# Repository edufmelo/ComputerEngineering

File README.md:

Academic projects and exercises developed during the Computer Engineering course.
(If there is any File/Folder that is not opening, it already has a specific repository on my GitHub.)
Last User - Eduardo Melo
Correct User - edufmelo

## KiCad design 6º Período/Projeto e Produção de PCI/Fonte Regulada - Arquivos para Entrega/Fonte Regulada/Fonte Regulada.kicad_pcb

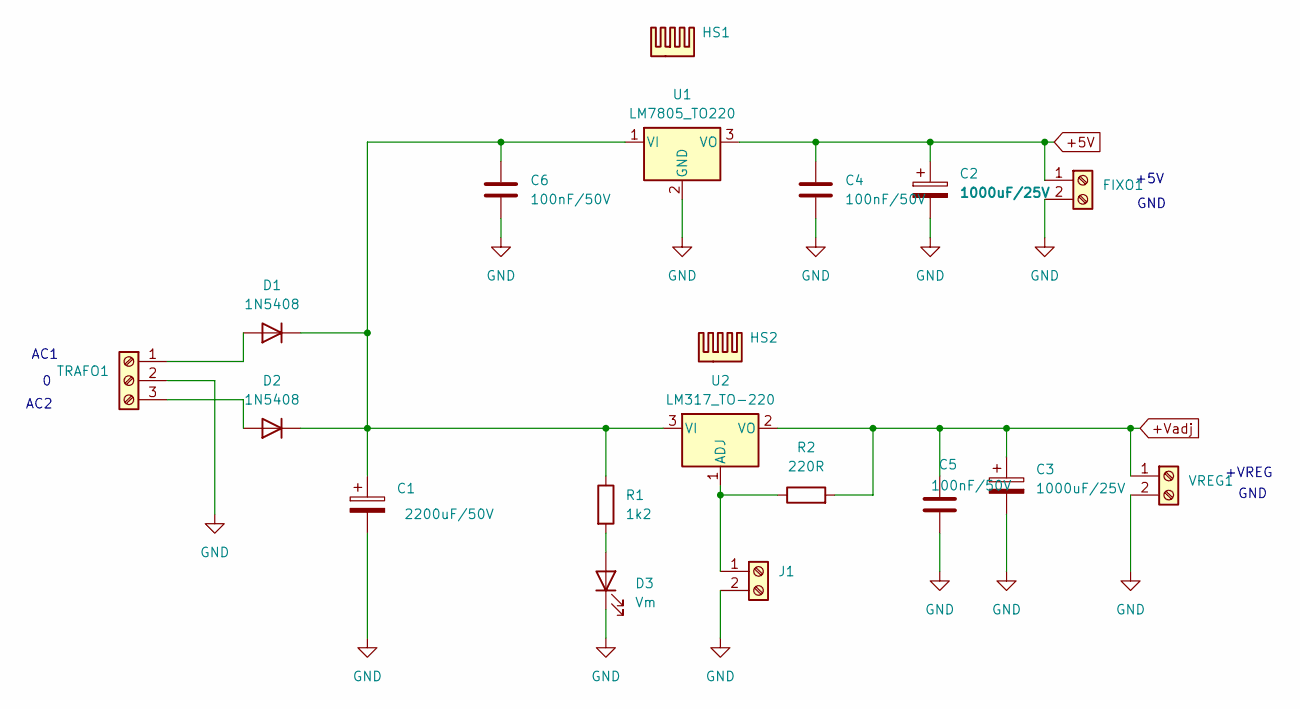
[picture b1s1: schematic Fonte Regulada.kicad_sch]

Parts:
C1: 2200uF/50V; CP_Radial_D17.0mm_P7.50mm
C2, C3: 1000uF/25V; CP_Radial_D10.0mm_P5.00mm
C4, C5, C6: 100nF/50V; C_Disc_D5.1mm_W3.2mm_P5.00mm
D1, D2: 1N5408; D_DO-201AD_P15.24mm_Horizontal
D3: Vm; LED_D5.0mm
FIXO1: TerminalBlock_Phoenix_MKDS-1,5-2-5.08_1x02_P5.08mm_Horizont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
HS1, HS2: Heatsink; Heatsink_35x26mm_1xFixation3mm_Fischer-SK486-35
J1: Screw_Terminal_01x02; TerminalBlock_Phoenix_MKDS-1,5-2-5.08_1x02_P5.08mm_Horizont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
R1: 1k2; R_Axial_DIN0207_L6.3mm_D2.5mm_P10.16mm_Horizontal
R2: 220R; R_Axial_DIN0207_L6.3mm_D2.5mm_P10.16mm_Horizontal
TRAFO1: TerminalBlock_Phoenix_MKDS-1,5-3-5.08_1x03_P5.08mm_Horizont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
U1: LM7805_TO220; TO-220-3_Horizontal_TabDown
U2: LM317_TO-220; TO-220-3_Horizontal_TabDown
VREG1: TerminalBlock_Phoenix_MKDS-1,5-2-5.08_1x02_P5.08mm_Horizont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

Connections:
+5V: C2.1, C4.1, FIXO1.1, U1.3 (VO)
+Vadj: C3.1, C5.1, R2.2, U2.2 (VO), VREG1.1
GND: C1.2, C2.2, C3.2, C4.2, C5.2, C6.2, D3.1 (K), FIXO1.2, J1.2, TRAFO1.2, U1.2 (GND), VREG1.2
unnamed: D1.2 (A), TRAFO1.1
unnamed: C1.1, C6.1, D1.1 (K), D2.1 (K), R1.1, U1.1 (VI), U2.3 (VI)
unnamed: D2.2 (A), TRAFO1.3
unnamed: D3.2 (A), R1.2
unnamed: J1.1, R2.1, U2.1 (ADJ)

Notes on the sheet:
+VREG
AC1
GND
+5V
AC2
GND

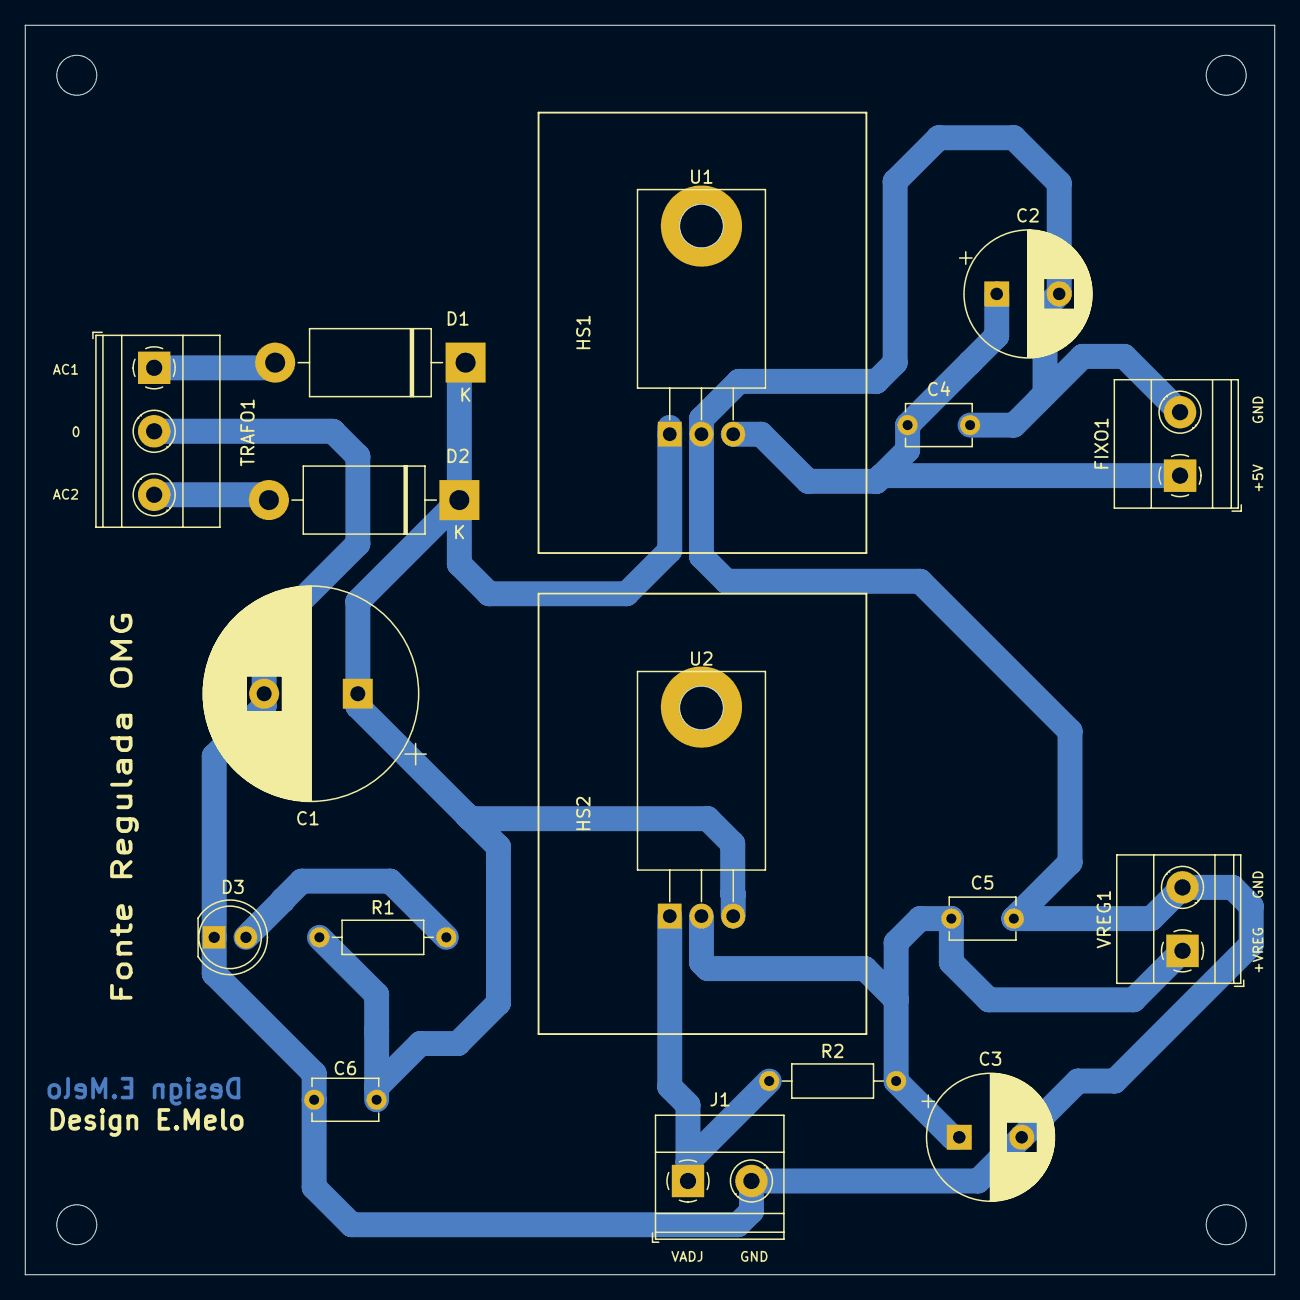
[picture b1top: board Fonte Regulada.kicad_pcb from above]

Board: 2 copper layers, 100.0 x 100.0 mm, 19 parts (0 on the bottom side), 8 nets.

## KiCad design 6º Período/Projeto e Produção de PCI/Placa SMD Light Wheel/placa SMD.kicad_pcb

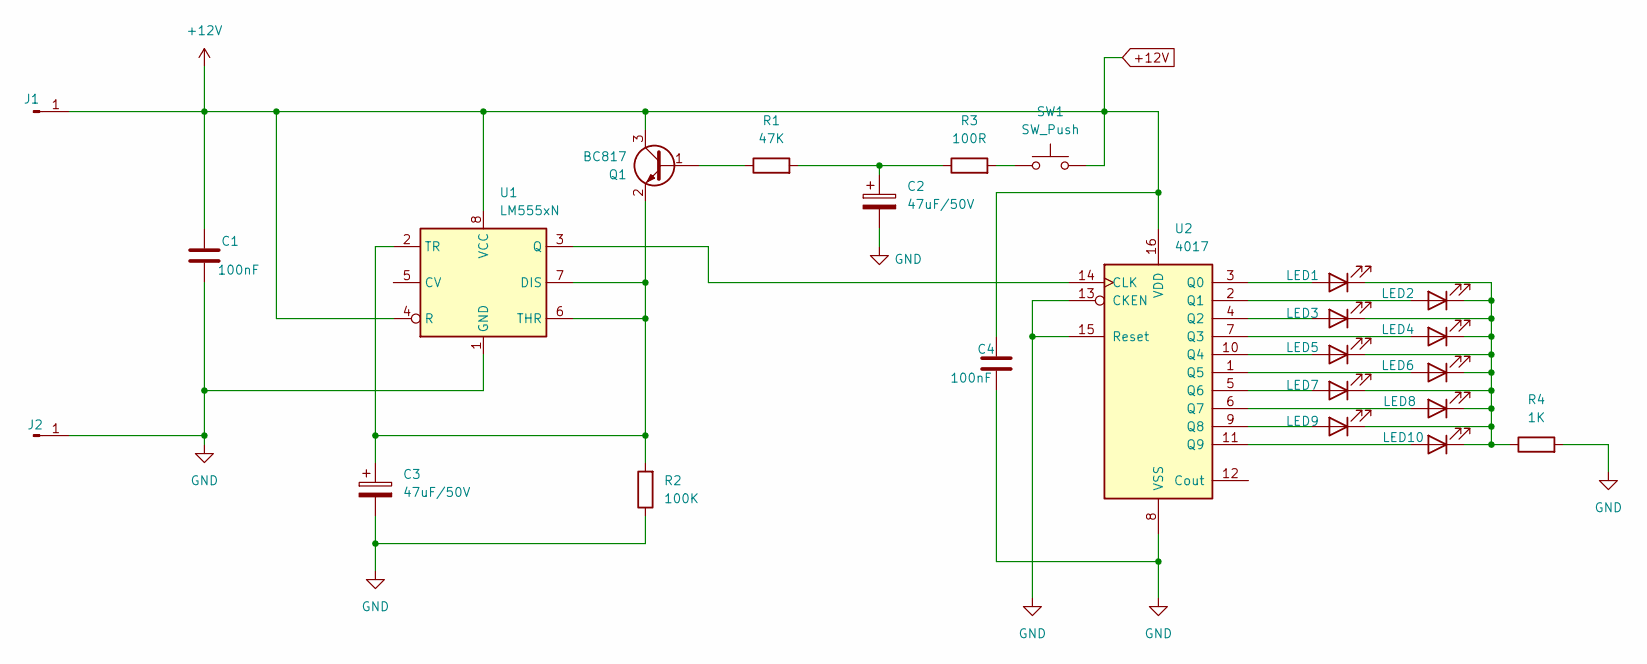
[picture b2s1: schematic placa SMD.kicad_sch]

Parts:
C1, C4: 100nF; C_0805_2012Metric
C2, C3: 47uF/50V; CP_Elec_5x5.9
D1: LED1; LED_0805_2012Metric
D2: LED2; LED_0805_2012Metric
D3: LED3; LED_0805_2012Metric
D4: LED4; LED_0805_2012Metric
D5: LED5; LED_0805_2012Metric
D6: LED6; LED_0805_2012Metric
D7: LED7; LED_0805_2012Metric
D8: LED8; LED_0805_2012Metric
D9: LED9; LED_0805_2012Metric
D10: LED10; LED_0805_2012Metric
J1, J2: Conn_01x01_Pin; PinHeader_1x01_P2.54mm_Vertical
Q1: BC817; SOT-23
R1: 47K; R_0805_2012Metric
R2: 100K; R_0805_2012Metric
R3: 100R; R_0805_2012Metric
R4: 1K; R_0805_2012Metric
SW1: SW_Push; SW_SPST_FSMSM
U1: LM555xN; SOIC-8-1EP_3.9x4.9mm_P1.27mm_EP2.29x3mm
U2: 4017; SOP-16_4.4x10.4mm_P1.27mm

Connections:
+12V: C1.1, C4.1, J1.1, Q1.3 (C), SW1.2, U1.4 (R), U1.8 (VCC), U2.16 (VDD); also elsewhere on the board
GND: C1.2, C2.2, C3.2, C4.2, J2.1, R2.1, R4.2, U1.1 (GND), U2.8 (VSS), U2.13 (CKEN), U2.15 (Reset); also elsewhere on the board
unnamed: C2.1, R1.2, R3.1
unnamed: D1.2 (A), U2.3 (Q0)
unnamed: D1.1 (K), D2.1 (K), D3.1 (K), D4.1 (K), D5.1 (K), D6.1 (K), D7.1 (K), D8.1 (K), D9.1 (K), D10.1 (K), R4.1
unnamed: D2.2 (A), U2.2 (Q1)
unnamed: D3.2 (A), U2.4 (Q2)
unnamed: D4.2 (A), U2.7 (Q3)
unnamed: D5.2 (A), U2.10 (Q4)
unnamed: D6.2 (A), U2.1 (Q5)
unnamed: D7.2 (A), U2.5 (Q6)
unnamed: D8.2 (A), U2.6 (Q7)
unnamed: D9.2 (A), U2.9 (Q8)
unnamed: D10.2 (A), U2.11 (Q9)
unnamed: Q1.1 (B), R1.1
unnamed: C3.1, Q1.2 (E), R2.2, U1.2 (TR), U1.6 (THR), U1.7 (DIS)
unnamed: R3.2, SW1.1
unnamed: U1.3 (Q), U2.14 (CLK)

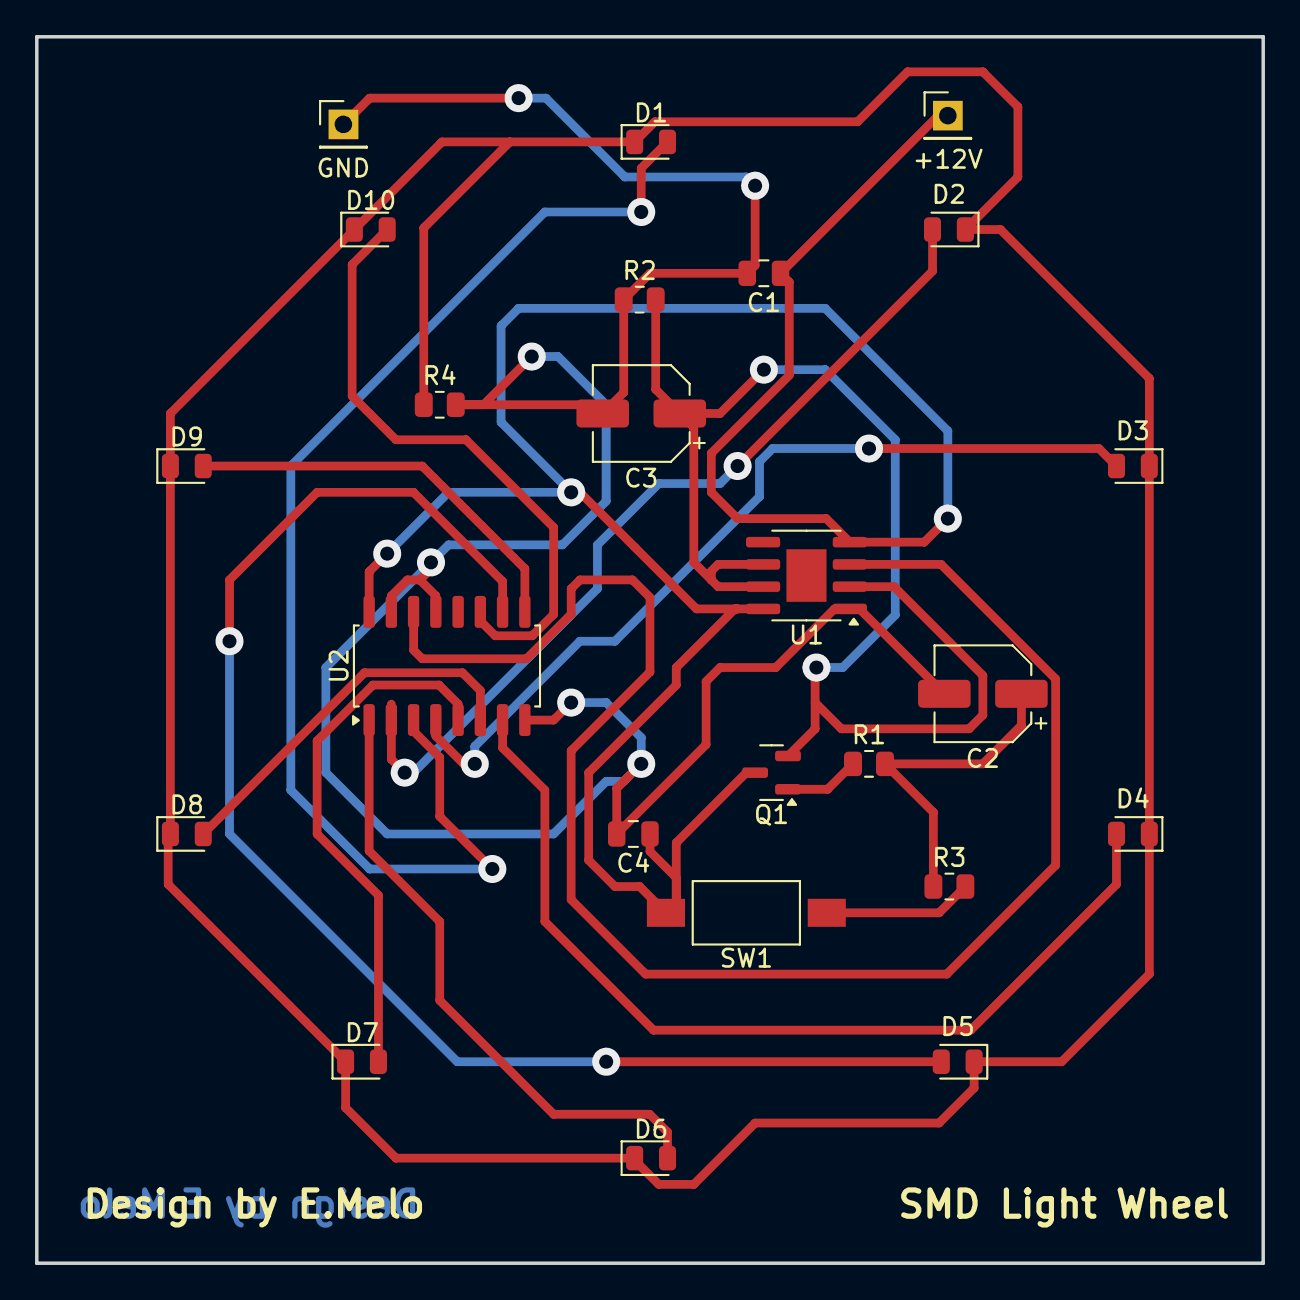
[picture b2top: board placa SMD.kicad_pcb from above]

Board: 2 copper layers, 70.0 x 70.0 mm, 24 parts (0 on the bottom side), 18 nets.

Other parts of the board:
+12V: Conn_01x01_Pin; PinHeader_1x01_P2.54mm_Vertical
GND: Conn_01x01_Pin; PinHeader_1x01_P2.54mm_Vertical

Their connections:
+12V: +12V.1; also elsewhere on the board
GND: GND.1; also elsewhere on the board

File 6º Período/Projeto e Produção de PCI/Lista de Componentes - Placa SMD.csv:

"Reference","Value","Datasheet","Footprint","Qty","DNP"
"C1,C4","100nF","~","Capacitor_SMD:C_0805_2012Metric","2",""
"C2,C3","47uF/50V","~","Capacitor_SMD:CP_Elec_5x5.9","2",""
"D1","LED1","~","LED_SMD:LED_0805_2012Metric","1",""
"D2","LED2","~","LED_SMD:LED_0805_2012Metric","1",""
"D3","LED3","~","LED_SMD:LED_0805_2012Metric","1",""
"D4","LED4","~","LED_SMD:LED_0805_2012Metric","1",""
"D5","LED5","~","LED_SMD:LED_0805_2012Metric","1",""
"D6","LED6","~","LED_SMD:LED_0805_2012Metric","1",""
"D7","LED7","~","LED_SMD:LED_0805_2012Metric","1",""
"D8","LED8","~","LED_SMD:LED_0805_2012Metric","1",""
"D9","LED9","~","LED_SMD:LED_0805_2012Metric","1",""
"D10","LED10","~","LED_SMD:LED_0805_2012Metric","1",""
"J1,J2","Conn_01x01_Pin","~","-- valores mistos --","2",""
"Q1","BC817","https://www.onsemi.com/pub/Collateral/BC818-D.pdf","Package_TO_SOT_SMD:SOT-23","1",""
"R1","47K","~","Resistor_SMD:R_0805_2012Metric","1",""
"R2","100K","~","Resistor_SMD:R_0805_2012Metric","1",""
"R3","100R","~","Resistor_SMD:R_0805_2012Metric","1",""
"R4","1K","~","Resistor_SMD:R_0805_2012Metric","1",""
"SW1","SW_Push","~","Button_Switch_SMD:SW_SPST_FSMSM","1",""
"U1","LM555xN","http://www.ti.com/lit/ds/symlink/lm555.pdf","Package_SO:SOIC-8_3.9x4.9mm_P1.27mm","1",""
"U2","4017","http://www.intersil.com/content/dam/Intersil/documents/cd40/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","Package_SO:SOP-16_4.4x10.4mm_P1.27mm","1",""

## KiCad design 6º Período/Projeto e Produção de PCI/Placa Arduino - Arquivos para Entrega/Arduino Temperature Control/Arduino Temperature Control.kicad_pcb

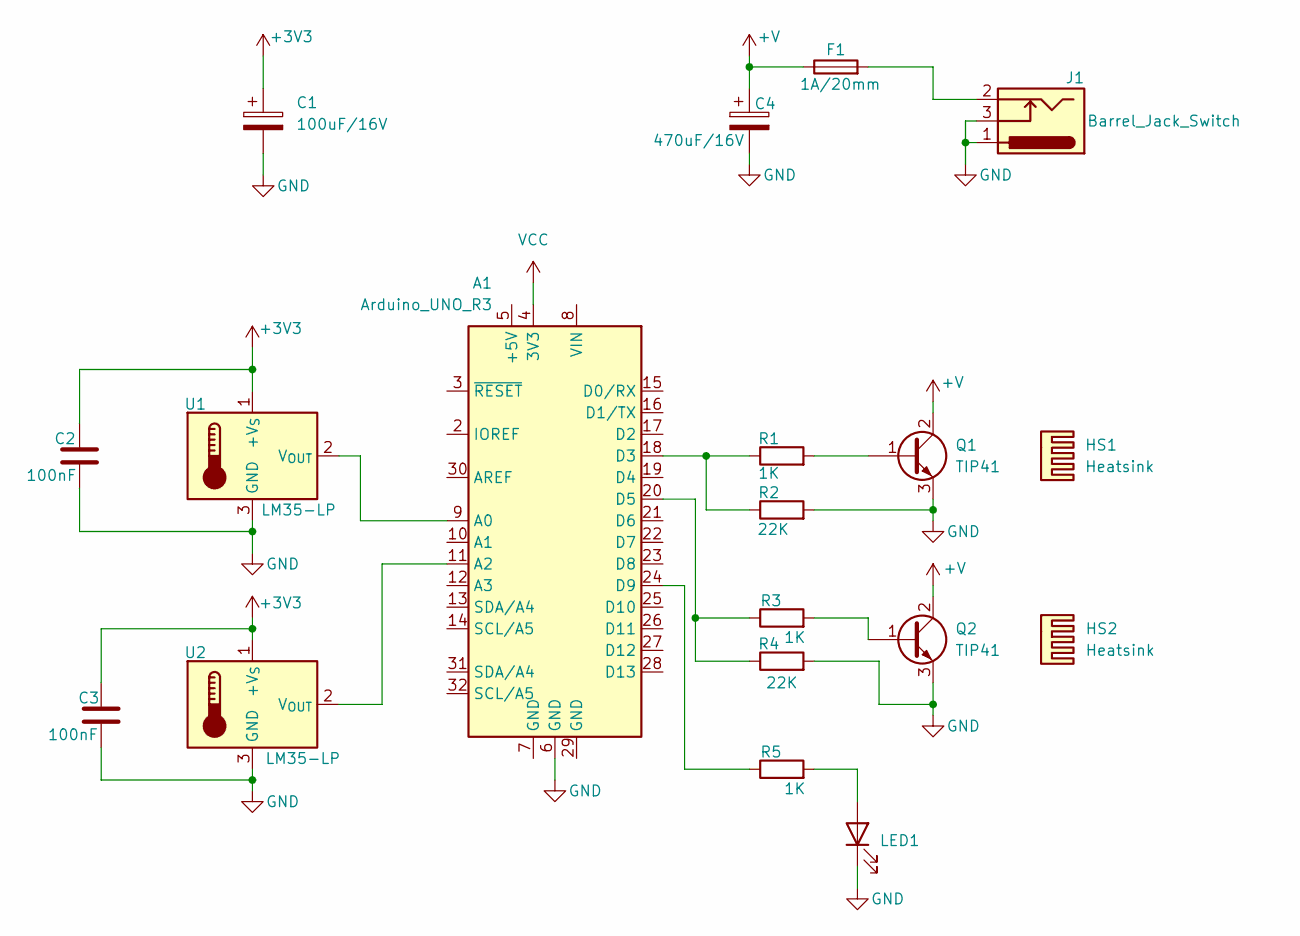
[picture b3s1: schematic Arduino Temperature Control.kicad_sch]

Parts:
A1: Arduino_UNO_R3
C1: 100uF/16V; CP_Radial_D10.0mm_P5.00mm
C2, C3: 100nF; C_Disc_D5.1mm_W3.2mm_P5.00mm
C4: 470uF/16V; CP_Radial_D10.0mm_P5.00mm
D1: LED1; LED_D5.0mm
F1: 1A/20mm; Fuseholder_Clip-5x20mm_Keystone_3517_Inline_P23.11x6.76mm_D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
HS1, HS2: Heatsink; Heatsink_Stonecold_HS-S02_13.21x9.53mm
J1: Barrel_Jack_Switch; BarrelJack_Horizontal
Q1, Q2: TIP41; TO-220-3_Vertical
R1, R3, R5: 1K; R_Axial_DIN0207_L6.3mm_D2.5mm_P10.16mm_Horizontal
R2, R4: 22K; R_Axial_DIN0207_L6.3mm_D2.5mm_P10.16mm_Horizontal
U1, U2: LM35-LP; TO-92_Inline

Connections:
+3V3: C1.1, C2.1, C3.1, U1.1 (+V_{S}), U2.1 (+V_{S})
+V: C4.1, F1.1, Q1.2 (C), Q2.2 (C)
GND: A1.6 (GND), C1.2, C2.2, C3.2, C4.2, D1.1 (K), J1.1, J1.3, Q1.3 (E), Q2.3 (E), R2.2, R4.2, U1.3 (GND), U2.3 (GND)
unnamed: A1.9 (A0), U1.2 (V_{OUT})
unnamed: A1.11 (A2), U2.2 (V_{OUT})
unnamed: A1.18 (D3), R1.1, R2.1
unnamed: A1.20 (D5), R3.1, R4.1
unnamed: A1.24 (D9), R5.1
unnamed: D1.2 (A), R5.2
unnamed: F1.2, J1.2
unnamed: Q1.1 (B), R1.2
unnamed: Q2.1 (B), R3.2
VCC: A1.4 (3V3)

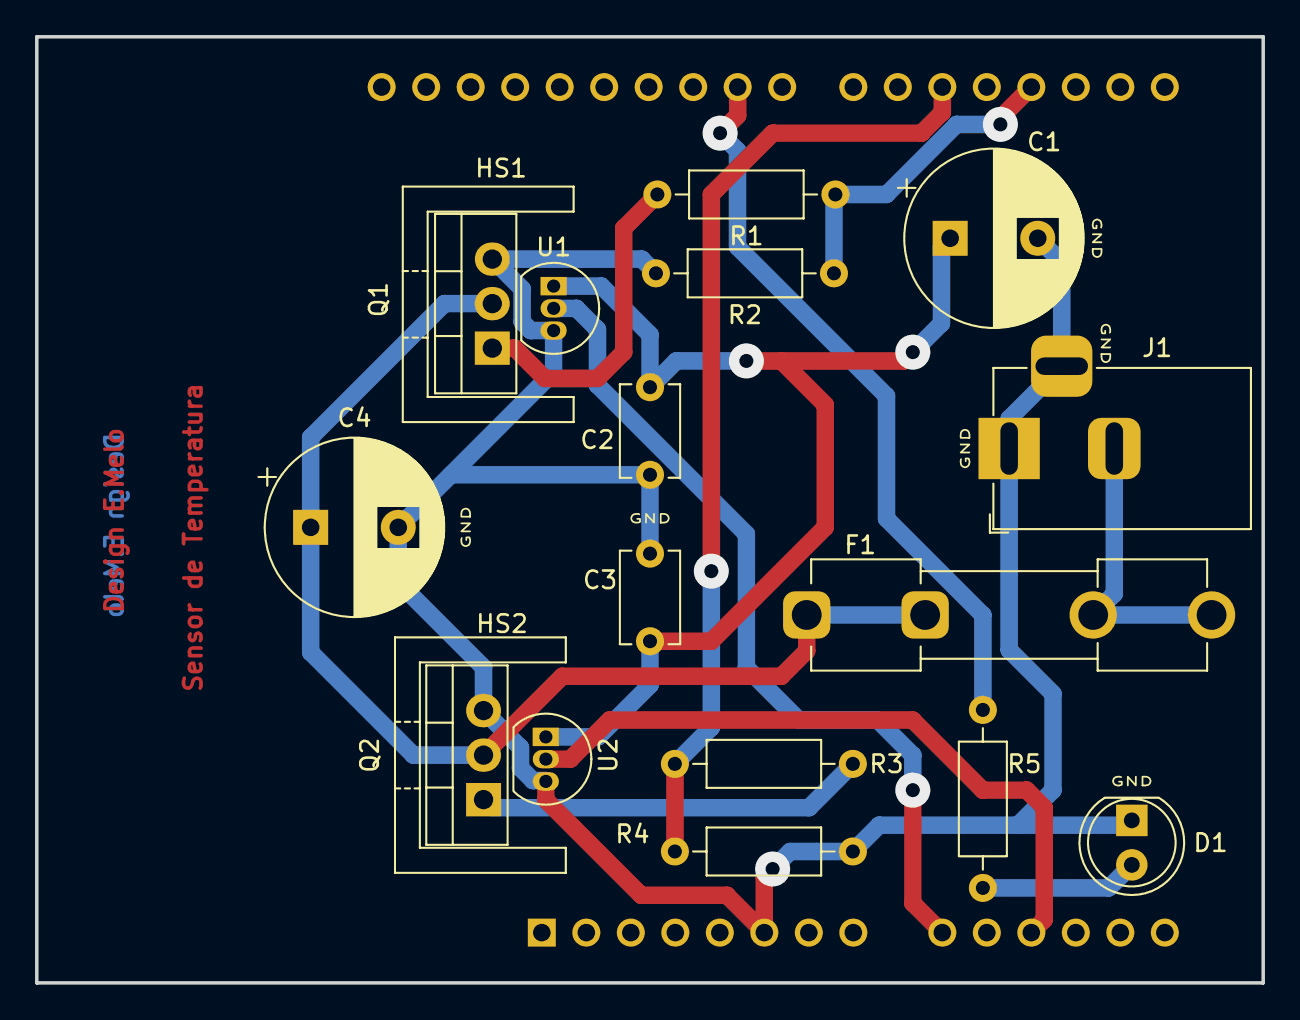
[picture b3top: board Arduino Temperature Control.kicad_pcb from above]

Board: 2 copper layers, 70.0 x 54.0 mm, 19 parts (1 on the bottom side), 12 nets.

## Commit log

2024-12-15 Atividades acadêmicas - 6º Semestre
2024-12-15 Projetos acadêmicos
2024-12-15 README.md
2024-12-15 Projetos/Atividade Acadêmicas
2024-12-15 Projetos e Atividade Acadêmicas
2024-12-15 Correcao pasta
2024-12-15 README.md
    Explain about any Files/Folders that are not opening.
2024-12-15 Projeto e exercícios acadêmicos atualizados
2024-12-15 Projeto e exercícios acadêmicos atualizados - edufmelo
2025-07-12 Atualização de projeto e atividades acadêmicas
